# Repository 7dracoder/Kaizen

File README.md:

# Kaizen

**Circuit boards from plain English, designed by AI agents that share one graph memory.**

Kaizen turns a sentence like *"USB-C powered temperature sensor with a status LED"* into a routed, manufacturable printed circuit board (Gerbers, BOM, KiCad project, 3D model). A team of agents plans, writes, checks and repairs the board. Everything they do (every attempt, failure, lesson, reusable subcircuit, config change and handoff) lands in one [FalkorDB](https://www.falkordb.com) graph, and **the graph decides what the agents are told**: before each build, Cypher traversals pick the lessons and blocks with real outcomes behind them. Every decision can be traced back to the path that caused it.

**Demo video:** [youtu.be/AILjiXgkjzo](https://youtu.be/AILjiXgkjzo) · **Blog:** [We let a graph decide what our AI agents remember](https://tanmaysahu3.medium.com/we-let-a-graph-decide-what-our-ai-agents-remember-1b7dd92b29a0) · Built for [Graph Hacks: Context for AI Agents](https://www.wemakedevs.org/hackathons/falkordb), Track 02 (Agent Memory and Coordination).

**FalkorDB is the only database.** It holds the agents' memory (episodic, semantic, procedural), their shared work queue, the request inbox, user accounts and one private graph per user. Take FalkorDB away and the agents have nothing to read, nothing to claim and nothing to remember.

### How Kaizen uses FalkorDB

| FalkorDB feature | What Kaizen does with it |
|---|---|
| Cypher traversals | Before every build, five queries decide which lessons, warnings and subcircuits the coder gets (see [How the agent queries it](#how-the-agent-queries-it)) |
| Vector indexes on nodes | `Lesson`, `Subcircuit` and failure nodes carry embeddings in the same graph, so similarity search and traversal run against one store |
| Atomic queries | A worker claims the next ready `WorkItem` or `Request` in one query: no locks, no double claims (tested with 12 workers racing for 6 steps) |
| Pub/sub | The web app writes a `Request` node and publishes its id; the worker wakes immediately instead of polling |
| Multigraph | One shared graph `kaizen` for agent memory, plus one isolated graph `kaizen_user_<hash>` per user for their history, in a single instance |
| Properties as the source of truth | Every record is a node; a `_rev` property makes updates compare-and-set, and edges are re-derived on every write so the graph never drifts |

## The problem

Most first-run PCBs get respun for the same handful of mistakes: missing I2C pull-ups, no decoupling capacitor next to a chip, an unconnected pin, a routing error. LLMs can write board code, but on their own they make those mistakes again and again. They have no memory of what failed last time, no way to check their own work against the requirements, and no record of *why* they made a choice.

## What Kaizen does

1. **Design**: a planner splits the spec into subcircuits, and a coder writes [tscircuit](https://tscircuit.com) code for each one. Deterministic tools compile it, autoroute it and run design-rule checks.
2. **Check**: a hidden checker grades the board against requirements the agents never see (connectivity, pull-ups, decoupling, DRC).
3. **Repair and learn**: a critic diagnoses each failure, proposes the smallest fix, and writes a **lesson** into the graph. Verified blocks become reusable **subcircuits**.
4. **Remember**: the next build retrieves the relevant lessons and subcircuits by vector search over the graph. Every run records which lessons and which harness version shaped it.
5. **Evolve**: a meta-agent proposes changes to the system's own rules and routing. A gate keeps a change only if the next batch scores better, and the full lineage stays in the graph.

| Board (3D view of a 20-part board built through the work queue) | Memory summary and the "why" trace of one build |
|---|---|
|  |  |

> The 3D board above was built by the long-horizon pipeline with **stand-in planner and coder** (`npm run finale -- --stub`, no model calls). Every screenshot is of the real running app on local FalkorDB.

## Architecture

```mermaid
flowchart TB
  subgraph Web["apps/web (Next.js)"]
    UI["Board, Harness, Memory, System pages"]
    API["API routes"]
  end
  subgraph Wk["apps/worker (Node)"]
    P["Planner"] --> C["Coder"] --> K["Checker + DRC"] --> CR["Critic"]
    CR --> C
    K --> A["Assembler"]
    K --> M["Meta-agent"] --> G["Config gate"]
    Q["Durable work queue"]
  end
  subgraph F["FalkorDB"]
    S[("Shared graph kaizen: memory, runs, configs, queue, requests")]
    U[("One graph per user: conversation history")]
  end
  UI --> API
  API -->|"read + Request nodes"| S
  API -->|"pub/sub wake-up"| Wk
  API --> U
  Wk <-->|"Cypher, vector search, atomic claims"| S
  Wk --> U
  P --> LLM["OpenAI-compatible model API"]
  C --> LLM
  CR --> LLM
  M --> LLM
  Wk -.->|optional| V["Voyage embeddings + rerank"]
```

## The graph (FalkorDB is where the decisions come from)

Every agent reads and writes one FalkorDB graph. Before the coder writes a line, Kaizen **traverses the graph** to decide what it gets told: the checks this kind of board tends to fail, the lessons learned from builds that failed them, the lessons that were in context when this spec passed, and the subcircuits that passing builds reused. Vector search only fills whatever space is left.

### Graph map

```mermaid
flowchart LR
  User((User)) -- REQUESTED --> Request
  Request -- PRODUCED --> Build
  Build -- FOR_SPEC --> Spec
  Run -- OF_BUILD --> Build
  Run -- BY_AGENT --> Agent
  Run -- UNDER --> Config
  Run -- FAILED_CHECK --> Check
  Run -- USED_LESSON --> Lesson
  Run -- REUSED --> Subcircuit
  Lesson -- LEARNED_FROM --> Build
  Config -- CHILD_OF --> Config
  Config -- HAS_RULE --> Rule
  BoardVersion -- OF_BUILD --> Build
  WorkItem -- PART_OF --> Build
  WorkItem -- DEPENDS_ON --> WorkItem
  WorkItem -- CLAIMED_BY --> Worker
  Agent -- HANDS_OFF_TO --> Agent
  Episode -- NEXT --> Episode
  Episode -- ABOUT --> Build
```

| Node | What it is | Memory type |
|---|---|---|
| `Run` | one attempt or agent step (compile, checks, critique, memory lookup), with model, tokens, failures | episodic |
| `Lesson`, `Subcircuit` | a learned design rule, a verified reusable block; both have FalkorDB vector indexes | semantic |
| `Config`, `Rule` | a version of the harness (rules, routing, workflow) and its lineage | procedural |
| `Build`, `Spec`, `Check`, `Agent` | hubs that connect everything about one board, one task, one kind of failure, one agent | — |
| `WorkItem`, `Worker` | steps of a long board and the worker holding each one: shared state between processes | coordination |
| `Request`, `User`, `Episode` | who asked for what; each user's own conversation history in a separate graph (`kaizen_user_<hash>`) | per-user |

### How the agent queries it

`apps/worker/src/harness/graph-context.ts` runs these before every build and stores the result (queries, row counts, and *why* each lesson was picked) on a `Run {stage: "memory"}` node, which the UI shows:

```cypher
// 1. Which checks have builds of this spec failed before?  (falls back to the most-failed checks overall)
MATCH (:Spec {id: $spec})<-[:FOR_SPEC]-(:Build)<-[:OF_BUILD]-(r:Run)-[:FAILED_CHECK]->(k:Check)
RETURN k.name AS check, count(r) AS times ORDER BY times DESC LIMIT 6

// 2. Which lessons were learned from builds that failed those checks?
MATCH (k:Check)<-[:FAILED_CHECK]-(:Run)-[:OF_BUILD]->(b:Build)<-[:LEARNED_FROM]-(l:Lesson)
WHERE k.name IN $checks AND l.active = true
RETURN l._id AS id, collect(DISTINCT k.name) AS checks, count(DISTINCT b) AS builds ORDER BY builds DESC

// 3. Which lessons were in context when this spec actually passed?
MATCH (:Spec {id: $spec})<-[:FOR_SPEC]-(:Build)<-[:OF_BUILD]-(r:Run {passed: true})-[:USED_LESSON]->(l:Lesson)
RETURN l._id AS id, count(r) AS wins ORDER BY wins DESC

// 4. Which subcircuits did passing builds of this spec reuse?
MATCH (:Spec {id: $spec})<-[:FOR_SPEC]-(:Build)<-[:OF_BUILD]-(r:Run {passed: true})-[:REUSED]->(s:Subcircuit)
RETURN s._id AS id, count(r) AS wins ORDER BY wins DESC

// 5. Then vector search fills the remaining slots
CALL db.idx.vector.queryNodes('Lesson', 'embedding', $k, vecf32($spec_embedding)) YIELD node, score
```

The picks go into the coder's prompt, the risky checks become a warning in the spec, and the run that uses them gets `USED_LESSON` edges, so the next build's query 3 can see whether they helped. Coordination uses the graph too: claiming a work item is one atomic query.

```cypher
MATCH (w:WorkItem) WHERE w.status = 'pending' AND size(w.waiting_on) = 0 AND w.board_id = $b
WITH w ORDER BY w.step ASC LIMIT 1
SET w.status = 'running', w.claimed_by = $worker, w.heartbeat = $t, w.attempts = w.attempts + 1
MERGE (k:Worker {id: $worker}) MERGE (w)-[:CLAIMED_BY]->(k)
RETURN properties(w)
```

### Where each decision comes from

| Decision an agent makes | Where it comes from in the graph | Code |
|---|---|---|
| Which design rules (lessons) the coder is told | Queries 2 and 3: lessons linked by `LEARNED_FROM` to builds that failed the risky checks, plus lessons with `USED_LESSON` edges from passing runs. Vector search only fills the leftover slots | `apps/worker/src/harness/graph-context.ts` |
| Which checks the spec warns about | Query 1: `FAILED_CHECK` counts for this spec, or across all builds for a new spec | `riskNote()` in the same file |
| Which verified subcircuit to reuse | Query 4: `REUSED` edges from passing runs of the same spec | same file |
| Which step a worker does next | One atomic claim on `WorkItem` nodes whose `DEPENDS_ON` steps are done | `apps/worker/src/harness/queue.ts` |
| Which board request a worker takes | Atomic claim on `Request` nodes, woken by FalkorDB pub/sub | `apps/worker/src/harness/requests.ts` |
| Which harness version runs, and whether a change stays | The current `Config` node and its `CHILD_OF` lineage; the gate writes keep/rollback back to it | `apps/worker/src/harness/gate.ts` |

### A real run: the graph fixing a mistake the model kept making

These are two real builds from this machine (GPT-4o-mini coder, Claude Sonnet 4.6 critic), read straight back out of FalkorDB.

**Build 1:** `t04_i2c_temp_breakout`. The memory was empty. The first attempt failed `pullups` and `tied` (floating I2C address pins) plus `decoupling`. The critic diagnosed it and wrote two `Lesson` nodes, each with a `LEARNED_FROM` edge to this build:

- *"Any I2C bus with an external header exposing SDA and SCL"* → add 4.7 kΩ pull-ups from SDA and SCL to 3.3 V
- *"Any I2C device with address-select pins (A0, A1, A2)"* → tie every address pin to VCC or GND

The second attempt passed every hidden check.

**Build 2:** a new free-text spec, *"USB-C powered I2C temperature sensor breakout with a status LED"*. The graph had never seen this spec, so query 1 returned nothing and Kaizen fell back to the most-failed checks overall. This is the record it stored on the build's `Run {stage: "memory"}` node:

```json
{
  "risky_checks": [ { "check": "pullups", "times": 2 }, { "check": "decoupling", "times": 2 }, { "check": "tied", "times": 2 } ],
  "picks": {
    "lessons": [
      { "id": "lesson_7773f765a0ee", "via": "graph",  "why": "learned from 1 build(s) that failed tied, decoupling, pullups" },
      { "id": "lesson_31226e95128e", "via": "graph",  "why": "learned from 1 build(s) that failed tied, decoupling, pullups" }
    ],
    "subcircuits": [ { "id": "sub_a243de72a4bd", "via": "vector", "why": "similar to the spec (score 0.88)" } ]
  }
}
```

Both lessons were chosen by **graph path**, not by text similarity. Result: across all 5 attempts, `pullups` and `tied` never failed again. `decoupling` failed every time, because no lesson for it had been written yet. That's the honest picture: the graph fixed the class of mistake it had evidence about, and only that one.

**Build 3:** *"I2C humidity sensor board, USB-C powered"*, also new to the graph. By now query 1 ranked `decoupling` as the riskiest check (failed 7 times across builds), so the spec carried that warning, and both I2C lessons were again picked by graph path. Attempt 1 failed `decoupling` and `separate`, the critic repaired it, and attempt 2 passed every hidden check, followed by three improve rounds that also passed. `pullups` and `tied` did not fail once.

**Query it yourself.** Everything above is plain FalkorDB data, so you can check it without the app (or in [FalkorDB Browser](https://browser.falkordb.com)):

```bash
# Why was each lesson handed to the coder? The decision record the agent stored before building
redis-cli GRAPH.QUERY kaizen "MATCH (r:Run {stage: 'memory'}) RETURN r.board_id, r._doc LIMIT 3"

# Which lesson came from which failed build?
redis-cli GRAPH.QUERY kaizen "MATCH (l:Lesson)-[:LEARNED_FROM]->(b:Build)<-[:OF_BUILD]-(r:Run)-[:FAILED_CHECK]->(k:Check) RETURN l.pattern, b.id, collect(DISTINCT k.name)"
```

**See it live:** open `/graph`, type a board and press **Build and watch**. Nodes arrive as the agents write them, the lessons the graph chose are ringed, and the side panel lists the exact Cypher, row counts and the reason for every pick. The panel also lists every query behind the view.

## How each core part works

- **Graph store** (`packages/graph`): records are FalkorDB nodes. Scalar fields are node properties, so Cypher can filter, index and traverse them. Nested data (failures, Circuit JSON) is stored as JSON on the node. Every write re-derives the node's relationships, so the graph never drifts from the records. A `_rev` counter makes read-modify-write updates compare-and-set.
- **Coordination**: FalkorDB runs each query atomically. Claiming the next ready work item ("pending, no unfinished dependency, lowest step") is one Cypher query, and so is claiming a spec request. Twelve concurrent workers racing for six steps never double-claim, and that's covered by a test. Heartbeats plus process checks make a killed worker's step resumable. Pub/sub wakes the worker the moment a request arrives.
- **Memory**: lessons, subcircuits and failure summaries are embedded and stored with FalkorDB vector indexes. Embeddings come from Voyage when a key is set. Otherwise a free local hashing embedder keeps memory working with lower recall. Vectors from different embedders are never compared.
- **Per-user memory**: each signed-in user gets an isolated graph holding their prompt and result history, kept across sessions. Deleting the account deletes that graph.
- **Traceability**: `/memory` runs graph traversals that answer *"why did this build turn out this way?"*: build ← runs → agent, harness version → rules, lessons used → where each lesson was learned, failed checks → how many other builds failed them.
- **Self-improvement**: the gate (`apps/worker/src/harness/gate.ts`) scores a proposed config on a fresh batch, spec by spec. It keeps the change, rolls it back, or rejects it if it weakens a check.

## Tech stack

TypeScript on Node 22 · FalkorDB 4.18 (graph + vector + pub/sub) · Next.js 16, React 19, Tailwind 4, React Three Fiber, react-force-graph, Phosphor icons · tscircuit (pinned) · Auth.js with a FalkorDB adapter · any OpenAI-compatible model gateway (runs on Nicrron: GPT-4o-mini for the coder, Claude Sonnet 4.6 for planner/critic/meta, voyage-4 embeddings) · LangSmith (optional)

## Folder layout

```
apps/web/          Next.js app: pages (board, live graph, memory, harness, system), API routes, 3D board scene, themes, FalkorDB auth adapter
apps/worker/       agents (planner, coder, critic, meta), tools (compile, DRC, metrics, router),
                   harness (config, gate, memory, graph-driven context, queue, requests), long-horizon pipeline, exporters
packages/graph/    FalkorDB client, record collections, schema and relationships, vector search,
                   per-user graphs, provenance traversals, network export for the live view
packages/types/    shared contracts (HarnessConfig, RunResult, ...)
checks/            hidden checker (never shown to agents)
specs/             public spec text      parts/  whitelisted parts
scripts/           setup, worker, finale, evolve, ablation, local FalkorDB launcher, key checker
```

## Run it locally

Everything runs on one machine: FalkorDB, the web app and the worker. The web app never calls a model. It writes a `Request` node to FalkorDB, the worker picks it up, runs the agents and writes every attempt back to the graph, and the web app reads it from there.

### 1. Prerequisites

- **Node.js 22.13 or newer** (`node -v` to check)
- **FalkorDB**, in one of two ways:
  - **Without Docker (recommended):** install `redis-server` (macOS: `brew install redis`, Linux: `sudo apt install redis-server`). `npm run db` loads the official FalkorDB module into it; the module is downloaded by the `falkordblite` package during `npm install`.
  - **With Docker:** `docker run -p 6379:6379 -v kaizen-falkordb:/data falkordb/falkordb`
- **An OpenAI-compatible model API key** (Nicrron, OpenRouter or similar). Only needed to design real boards; everything else works without it.
- Optional: `redis-cli` (comes with Redis) to run Cypher against the graph yourself.

### 2. Install

```bash
git clone https://github.com/7dracoder/Kaizen.git
cd Kaizen
npm install          # installs every workspace and builds packages/graph and packages/types
```

### 3. Configure

```bash
cp .env.example .env                  # used by the worker and the scripts
cp .env.example apps/web/.env.local   # used by the web app
```

Both files are gitignored. The defaults already point at a local FalkorDB (`FALKORDB_URL=redis://127.0.0.1:6379`, graph `kaizen`). To design boards, fill these in `.env`:

```bash
AI_BASE_URL=https://api.nicrron.ai/v1        # or https://openrouter.ai/api/v1
AI_API_KEY=<your key>
MODEL_CHEAP=openai/gpt-4o-mini               # the coder
MODEL_STRONG=anthropic/claude-sonnet-4-6     # planner and critic
EMBED_MODEL=voyage/voyage-4                  # optional: better lesson recall
```

Leave the `AUTH_*` variables empty to run in anonymous mode (no sign-in). See [API keys](#api-keys) for what each one unlocks.

### 4. Start FalkorDB (terminal 1)

```bash
npm run db
```

It prints `FalkorDB on 127.0.0.1:6379, data in .data/falkordb` and keeps running. Data is persisted, so the graph's memory survives restarts. Skip this if you started the Docker image.

### 5. Create the graph (once)

```bash
npm run setup
```

This creates the indexes, unique-id constraints and vector indexes, harness config v0, the public specs, and the agents as `Agent` nodes. It is safe to run again. Check it:

```bash
redis-cli GRAPH.QUERY kaizen "MATCH (n) RETURN labels(n)[0] AS label, count(n) ORDER BY label"
```

### 6. Start the web app (terminal 2)

```bash
npm run dev
```

Open http://localhost:3000. The **System** tab should show FalkorDB as "Connected"; http://localhost:3000/api/health reports the connection and the record counts.

### 7. Start the worker (terminal 3)

```bash
npm run worker
```

It prints `waiting for spec requests (concurrency 3)`. It is safe to stop and restart: an interrupted request resumes where it stopped.

### 8. Build a board

1. On the **Board** tab, pick one of the examples under the prompt (or type your own) and press **Build →**.
2. The worker log shows the request within a few seconds. A build takes one to three minutes.
3. Switch tabs while it runs; they all follow the same board:
   - **Graph**: the lessons the graph picked for this build and why (graph path or vector search), and the risky checks.
   - **Board**: the 3D board as each attempt lands, and the hidden-check result.
   - **Harness**: every stage, model, token count and cost.
   - **Memory**: this build's neighbourhood in the graph: runs, failed checks, lessons used and where they were learned.

You can also start a build from the **Graph** tab: type a board and press **Build and watch**.

### 9. Look at the graph directly

```bash
# requests by status
redis-cli GRAPH.QUERY kaizen "MATCH (q:Request) RETURN q.status, count(q)"

# every attempt of one board and the checks it failed (board id from the Board tab)
redis-cli GRAPH.QUERY kaizen "MATCH (r:Run {board_id:'<board id>'}) OPTIONAL MATCH (r)-[:FAILED_CHECK]->(k:Check) WITH r, collect(k.name) AS failed RETURN r.stage, r.passed, failed, r.ts ORDER BY r.ts"
```

### 10. Teach it and review what it learned

Free-text builds from the web app use lessons but never write them. Lessons come from training specs, run from the CLI:

```bash
npm run board -- t04_i2c_temp_breakout               # run one training spec; the critic stores lessons
npm run board -- t04_i2c_temp_breakout --no-memory   # same spec as if memory were empty
npm run lessons                                      # list every lesson
npm run lessons -- retire <id> "<why>"               # stop using a bad lesson (kept, marked inactive)
npm run lessons -- restore <id>                      # use it again
```

Training specs are in `specs/specs.json` (`t01_led_indicator` to `t08_i2c_two_devices`, and more).

### Without an API key

You can still run the stand-in 20-part board through the real queue and checks, open it in 3D, and browse the memory graph, the system and harness views, and every test:

```bash
npm run finale -- --stub --reset   # free: planner and coder stand-ins, real checks, real queue
npm run green                      # with keys: one real call per configured service
```

### Troubleshooting

- **`redis-server not found`**: install Redis (step 1), or use the Docker image.
- **Pages say "Disconnected"**: FalkorDB isn't running, or `FALKORDB_URL` in `apps/web/.env.local` is wrong.
- **A build stays "queued"**: the worker isn't running (step 7).
- **A build fails with a model error**: check `AI_API_KEY`, `AI_BASE_URL` and the model names in `.env`, then run `npm run green`.
- **Port 6379 is taken**: `FALKORDB_PORT=6380 npm run db`, and set `FALKORDB_URL=redis://127.0.0.1:6380` in both env files.

## API keys

| Key | Priority | Unlocks | Without it |
|---|---|---|---|
| `FALKORDB_URL` | required | everything (defaults to local `redis://127.0.0.1:6379`) | nothing works; pages show "Disconnected" |
| `AI_API_KEY` (+ `AI_BASE_URL`, e.g. `https://api.nicrron.ai/v1`) | 1 | the agents: designing boards from the web or CLI | builds fail with a clear message |
| `EMBED_MODEL` (same gateway key) or `VOYAGE_API_KEY` | 2 | semantic embeddings for memory (`voyage/voyage-4`, 1024 dims); Voyage direct adds reranking | local hashing embedder (works, lower recall) |
| `AUTH_SECRET` + `AUTH_GOOGLE_ID`/`AUTH_GOOGLE_SECRET` or `AUTH_RESEND_KEY` | 3 | sign-in, per-user memory graphs and build limits | anonymous mode, no personal history |
| `LANGSMITH_API_KEY` | 4 | traces of every model call | no tracing |

## API routes

| Route | Returns |
|---|---|
| `GET /api/health` | FalkorDB connection, record counts, user-graph count, active embedder |
| `GET /api/graph/network[?board_id=]` | the graph as nodes + links (one build's neighbourhood, or the whole memory) plus the Cypher that produced it |
| `GET /api/graph` | memory summary: node/relationship counts, lessons ranked by passing uses, most-failed checks, config lineage |
| `GET /api/graph?board_id=` | provenance trace of one build (nodes + edges) |
| `GET /api/history` | the signed-in user's conversation history from their own graph |
| `GET/POST /api/spec`, `GET /api/spec/:id` | spec list, submit a build (`{ text }` or `{ spec_id }`), request status |
| `GET /api/runs?since=&board_id=` | run feed |
| `GET /api/boards`, `GET /api/boards/:id` | board index, one board adapted for the 3D scene |
| `GET /api/boards/:id/deliverables[?file=]` | manifest and files (Gerbers, BOM, KiCad, ...) |
| `GET /api/harness` | every config version and the current one |
| `GET /api/memory` | active lessons and the subcircuit library |
| `GET /api/queue?board_id=` | work items with stale-worker detection |

## Tests

```bash
npm test             # everything below
npm run test:graph   # FalkorDB integration: store, relationships, vector search, per-user isolation,
                     # concurrent queue and request claims, lessons (needs `npm run db`; uses a throwaway graph)
npm run test:checks  # hidden checker     npm run test:gate     config gate
npm run test:critic  npm run test:planner  npm run test:assembler  npm run test:export  npm run test:meta
npm run typecheck && npm run smoke
```

## Roadmap

- Feed each user's history back into the planner, so follow-ups like "make it smaller" refine the previous board
- Graph algorithms as agent tools (PageRank over lessons, community detection over failure patterns)
- Read-only Cypher tool access for the critic and meta-agent
- Hosted FalkorDB with one graph per organisation, plus team-shared libraries
- More parts, 4-layer boards, SPICE checks in the loop

## Security

- Secrets live only in `.env` / `apps/web/.env.local` (gitignored). The app never sends keys to the browser, and all model and database calls run server-side.
- The web app writes only spec requests and accounts. Design state has one writer, the worker.
- With sign-in configured, building requires a session, with per-user and global caps on queued builds (they protect the model budget).
- **Without sign-in the app is anonymous, so anyone who can reach it can queue builds that spend your model budget.** Don't expose it publicly without auth.
- Local FalkorDB binds to 127.0.0.1 with no password. Any hosted instance must have a password and TLS.
- Hidden checks never reach the agents, the graph or the model.

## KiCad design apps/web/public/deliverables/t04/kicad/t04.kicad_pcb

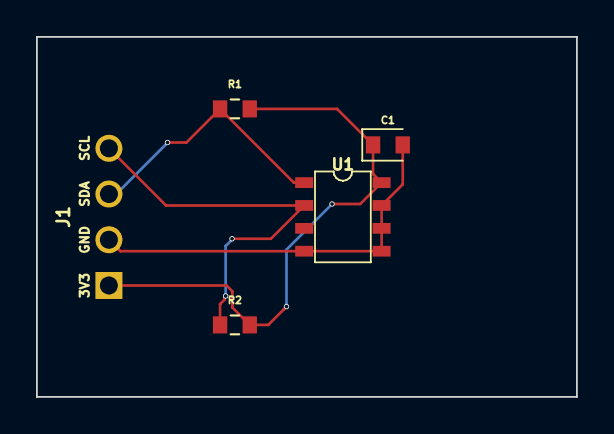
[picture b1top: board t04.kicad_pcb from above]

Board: 2 copper layers, 30.0 x 20.0 mm, 5 parts (0 on the bottom side), 4 nets.

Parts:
C1: 100nF; capacitor_cap0603
J1: J1; pin_header_pinrow4
R1, R2: 4.7kΩ; resistor_res0603
U1: LM75B

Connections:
GND: C1.2, J1.2, U1.4, U1.5, U1.6, U1.7
SCL: J1.4, R2.1, U1.2
SDA: J1.3, R1.1, U1.1
V3V3: C1.1, J1.1, R1.2, R2.2, U1.8

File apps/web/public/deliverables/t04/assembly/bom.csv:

"Designator","Comment","Value","Footprint"
"J1","","","pinrow4"
"U1","LM75B","","soic8"
"C1","100n","100n","cap0603"
"R1","4.7k","4.7k","res0603"
"R2","4.7k","4.7k","res0603"
